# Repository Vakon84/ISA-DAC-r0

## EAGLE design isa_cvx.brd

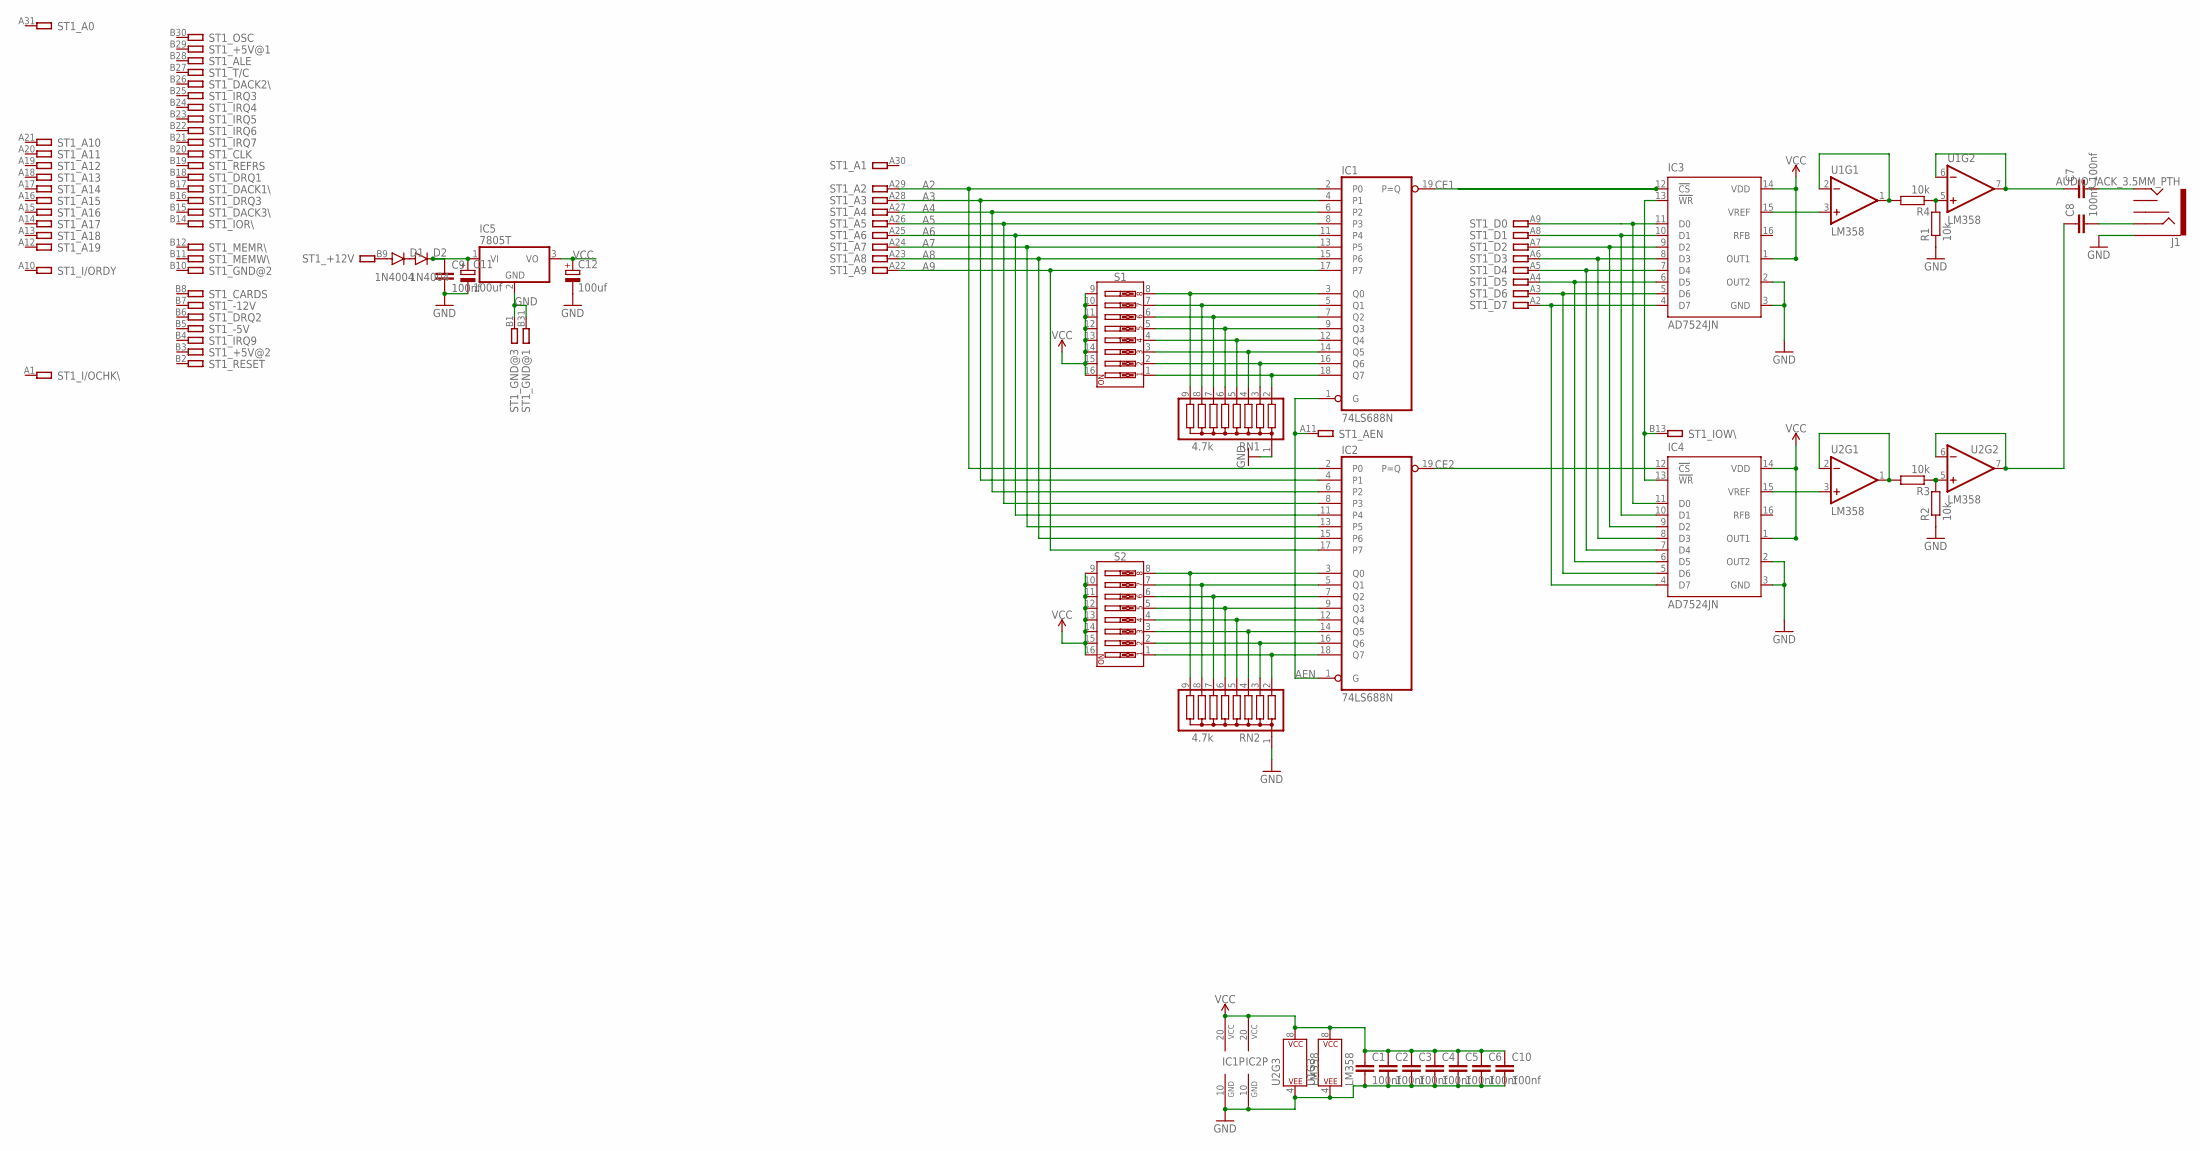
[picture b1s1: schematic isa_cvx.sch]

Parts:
C1, C2, C3, C4, C5, C6, C7, C8, C9, C10: 100nf; C2.5-2
C11, C12: 100uf; E2,5-5
D1, D2: 1N4004; DO41-10
IC1, IC2: 74LS688N; DIL20
IC3, IC4: AD7524JN; DIL16
IC5: 7805T; TO220H
J1: AUDIO_JACK_3.5MM_PTH; AUDIO-JACK
R1, R2, R3, R4: 10k; 0207/10
RN1, RN2: 4.7k; SIL9
S1, S2: DIP-08-PTH; DIPSWITCH-08
ST1: IBM8BIT
U1, U2: LM358; DIP08

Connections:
A2: IC1.2 (P0), IC2.2 (P0), ST1.A29
A3: IC1.4 (P1), IC2.4 (P1), ST1.A28
A4: IC1.6 (P2), IC2.6 (P2), ST1.A27
A5: IC1.8 (P3), IC2.8 (P3), ST1.A26
A6: IC1.11 (P4), IC2.11 (P4), ST1.A25
A7: IC1.13 (P5), IC2.13 (P5), ST1.A24
A8: IC1.15 (P6), IC2.15 (P6), ST1.A23
A9: IC1.17 (P7), IC2.17 (P7), ST1.A22
AEN: IC1.1 (G), IC2.1 (G), ST1.A11
CE1: IC1.19 (P=Q), IC3.12 (!CS)
CE2: IC2.19 (P=Q), IC4.12 (!CS)
GND: C1.2, C2.2, C3.2, C4.2, C5.2, C6.2, C9.2, C10.2, C11.-, C12.-, IC1.10 (GND), IC2.10 (GND), IC3.2 (OUT2), IC3.3 (GND), IC4.2 (OUT2), IC4.3 (GND), IC5.2 (GND), J1.SLEEVE, R1.1, R2.1, RN1.1, RN2.1, ST1.B1, ST1.B31, U1.4 (P$V-), U2.4 (P$V-)
unnamed: IC3.11 (D0), IC4.11 (D0), ST1.A9
unnamed: IC3.10 (D1), IC4.10 (D1), ST1.A8
unnamed: IC3.9 (D2), IC4.9 (D2), ST1.A7
unnamed: IC3.8 (D3), IC4.8 (D3), ST1.A6
unnamed: IC3.7 (D4), IC4.7 (D4), ST1.A5
unnamed: IC3.6 (D5), IC4.6 (D5), ST1.A4
unnamed: IC3.13 (!WR), IC4.13 (!WR), ST1.B13
unnamed: IC3.4 (D7), IC4.4 (D7), ST1.A2
unnamed: D1.A, ST1.B9
unnamed: IC1.3 (Q0), RN1.9, S1.8
unnamed: IC1.5 (Q1), RN1.8, S1.7
unnamed: IC1.7 (Q2), RN1.7, S1.6
unnamed: IC1.9 (Q3), RN1.6, S1.5
unnamed: IC1.12 (Q4), RN1.5, S1.4
unnamed: IC1.14 (Q5), RN1.4, S1.3
unnamed: IC1.16 (Q6), RN1.3, S1.2
unnamed: IC1.18 (Q7), RN1.2, S1.1
unnamed: IC2.3 (Q0), RN2.9, S2.8
unnamed: IC2.5 (Q1), RN2.8, S2.7
unnamed: IC2.7 (Q2), RN2.7, S2.6
unnamed: IC2.9 (Q3), RN2.6, S2.5
unnamed: IC2.12 (Q4), RN2.5, S2.4
unnamed: IC2.14 (Q5), RN2.4, S2.3
unnamed: IC2.16 (Q6), RN2.3, S2.2
unnamed: IC2.18 (Q7), RN2.2, S2.1
unnamed: IC3.5 (D6), IC4.5 (D6), ST1.A3
unnamed: IC3.15 (VREF), U1.3 (+IN)
unnamed: C9.1, C11.+, D2.C, IC5.1 (VI)
unnamed: D1.C, D2.A
unnamed: R4.2, U1.1 (OUT), U1.2 (-IN)
unnamed: IC4.15 (VREF), U2.3 (+IN)
unnamed: R3.2, U2.1 (OUT), U2.2 (-IN)
unnamed: C8.1, U2.6 (-IN), U2.7 (OUT)
unnamed: C7.1, U1.6 (-IN), U1.7 (OUT)
unnamed: R1.2, R4.1, U1.5 (+IN)
unnamed: R2.2, R3.1, U2.5 (+IN)
unnamed: C7.2, J1.TIP
unnamed: C8.2, J1.RING
VCC: C1.1, C2.1, C3.1, C4.1, C5.1, C6.1, C10.1, C12.+, IC1.20 (VCC), IC2.20 (VCC), IC3.1 (OUT1), IC3.14 (VDD), IC4.1 (OUT1), IC4.14 (VDD), IC5.3 (VO), S1.9, S1.10, S1.11, S1.12, S1.13, S1.14, S1.15, S1.16, S2.9, S2.10, S2.11, S2.12, S2.13, S2.14, S2.15, S2.16, U1.8 (P$V+), U2.8 (P$V+)

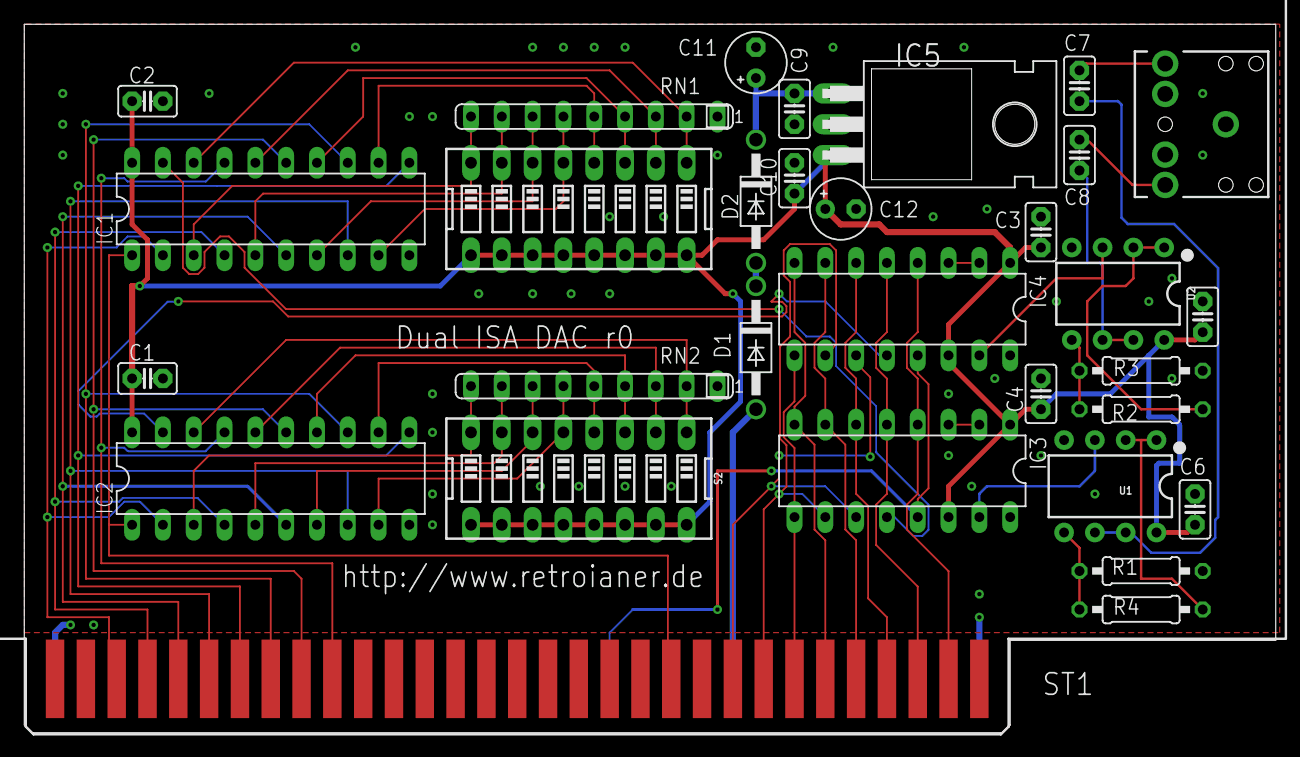
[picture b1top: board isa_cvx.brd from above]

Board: 2 copper layers, 103.2 x 58.4 mm, 31 parts (0 on the bottom side), 51 nets.

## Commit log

2020-10-04 Add files via upload
    DAC in Action:
    https://www.youtube.com/watch?v=qWZV97xx3eA
    https://www.youtube.com/watch?v=hvpyohpkQ3E
    https://www.youtube.com/watch?v=9P1nS3z2giU
    https://www.youtube.com/watch?v=FnlOKTi11Zk
2020-12-13 Add files via upload
    Schematic and PCB for ISA DAC r0 Card
2020-12-13 Delete LICENSE
    Wrong License

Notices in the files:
parts and their libraries:
SparkFun-Switches: Licensing: Creative Commons ShareAlike 4.0 International - https://creativecommons.org/licenses/by-sa/4.0
